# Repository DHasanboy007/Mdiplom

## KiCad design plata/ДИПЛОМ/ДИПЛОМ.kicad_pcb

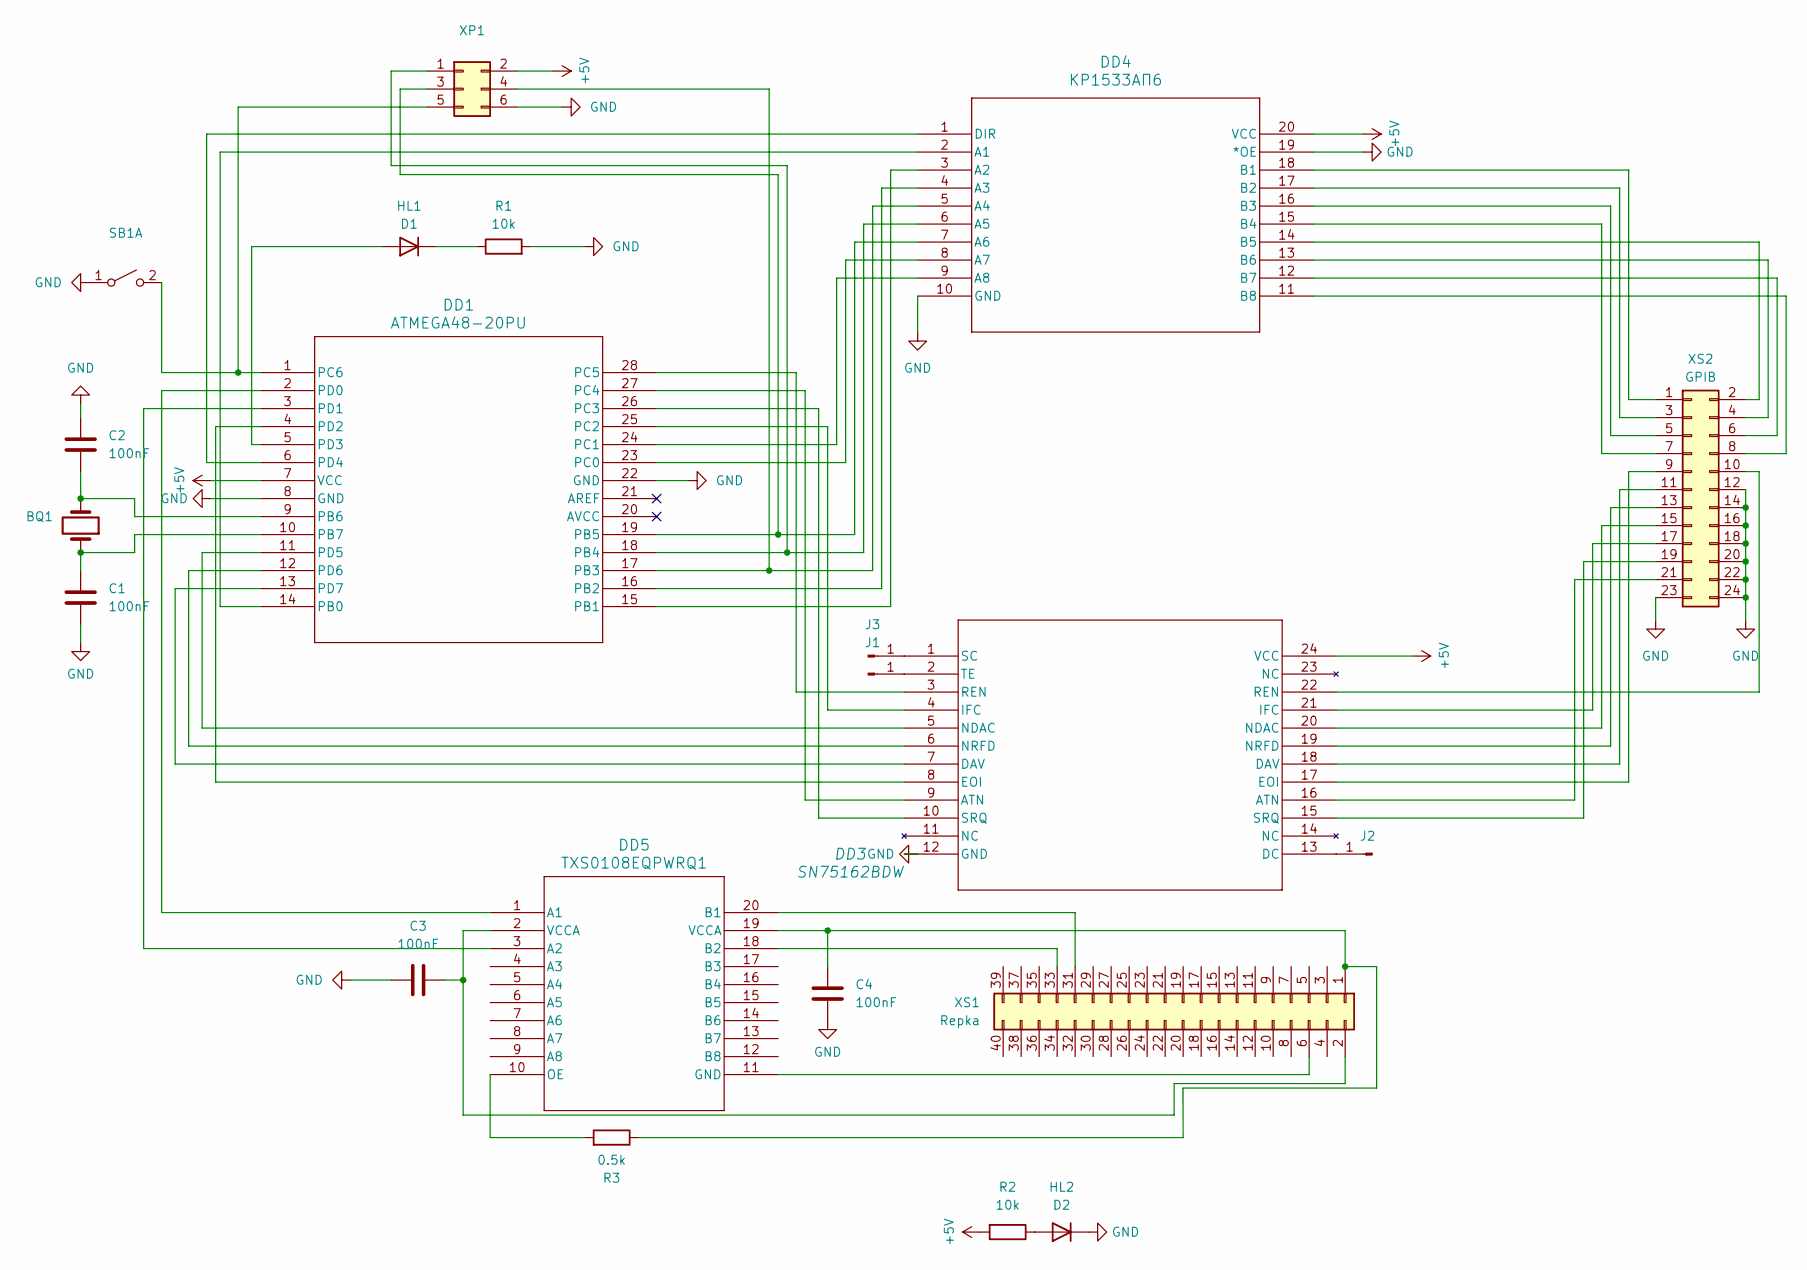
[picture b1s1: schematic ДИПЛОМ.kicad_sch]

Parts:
BQ1: Crystal; Crystal_HC49-U_Vertical
C1, C2, C3, C4: 100nF; C_0805_2012Metric
DD1: ATMEGA48-20PU; DIP-28_W7.62mm_SMDSocket_SmallPads
DD3: SN75162BDW; SOIC-24W_7.5x15.4mm_P1.27mm
DD4: КР1533АП6; DIP-20_W7.62mm
DD5: TXS0108EQPWRQ1; TSSOP-20_4.4x6.5mm_P0.65mm
HL1: D1; D_SOD-123
HL2: D2; D_SOD-123
J1, J2, J3: Conn_01x01_Pin; PinHeader_1x01_P2.54mm_Vertical
R1, R2: 10k; R_0805_2012Metric
R3: 0.5k; R_0805_2012Metric
SB1: SW_DPST_x2; SW_Push_1P1T_NO_E-Switch_TL3301NxxxxxG
XP1: Conn_02x03_Odd_Even; PinHeader_2x03_P2.54mm_Vertical
XS1: Repka; PinSocket_2x20_P2.54mm_Vertical
XS2: GPIB; PinSocket_2x12_P2.54mm_Vertical

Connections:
+5V: DD1.7 (VCC), DD3.24 (VCC), DD4.20 (VCC), R2.2, XP1.2
GND: C1.2, C2.1, C3.2, C4.2, DD1.8 (GND), DD1.22 (GND), DD3.12 (GND), DD4.10 (GND), DD4.19 (*OE), HL2.1 (K), R1.2, SB1.1 (A), XP1.6, XS2.12, XS2.14, XS2.16, XS2.18, XS2.20, XS2.22, XS2.23, XS2.24
unnamed: DD1.14 (PB0), DD4.2 (A1)
unnamed: DD1.15 (PB1), DD4.3 (A2)
unnamed: DD1.16 (PB2), DD4.4 (A3)
unnamed: DD1.17 (PB3), DD4.5 (A4), XP1.4
unnamed: DD1.18 (PB4), DD4.6 (A5), XP1.1
unnamed: DD1.19 (PB5), DD4.7 (A6), XP1.3
unnamed: BQ1.2, C2.2, DD1.9 (PB6)
unnamed: BQ1.1, C1.1, DD1.10 (PB7)
unnamed: DD1.23 (PC0), DD4.8 (A7)
unnamed: DD1.24 (PC1), DD4.9 (A8)
unnamed: DD1.25 (PC2), DD3.4 (IFC)
unnamed: DD1.26 (PC3), DD3.10 (SRQ)
unnamed: DD1.27 (PC4), DD3.9 (ATN)
unnamed: DD1.28 (PC5), DD3.3 (REN)
unnamed: DD1.1 (PC6), SB1.2 (B), XP1.5
unnamed: DD1.2 (PD0), DD5.1 (A1)
unnamed: DD1.3 (PD1), DD5.3 (A2)
unnamed: DD1.4 (PD2), DD3.8 (EOI)
unnamed: DD1.5 (PD3), HL1.2 (A)
unnamed: DD1.6 (PD4), DD4.1 (DIR)
unnamed: DD1.11 (PD5), DD3.5 (NDAC)
unnamed: DD1.12 (PD6), DD3.6 (NRFD)
unnamed: DD1.13 (PD7), DD3.7 (DAV)
unnamed: DD3.13 (DC), J2.1
unnamed: DD3.1 (SC), J3.1
unnamed: DD3.2 (TE), J1.1
unnamed: DD4.18 (B1), XS2.1
unnamed: DD4.17 (B2), XS2.3
unnamed: DD4.16 (B3), XS2.5
unnamed: DD4.15 (B4), XS2.7
unnamed: DD4.14 (B5), XS2.2
unnamed: DD4.13 (B6), XS2.4
unnamed: DD4.12 (B7), XS2.6
unnamed: DD4.11 (B8), XS2.8
unnamed: DD5.20 (B1), XS1.31
unnamed: DD5.18 (B2), XS1.33
unnamed: DD5.11 (GND), XS1.6
unnamed: DD5.10 (OE), R3.2
unnamed: HL1.1 (K), R1.1
unnamed: HL2.2 (A), R2.1
unnamed: C4.1, DD5.19 (VCCA), R3.1, XS1.1
unnamed: C3.1, DD5.2 (VCCA), XS1.2
unnamed: DD3.17 (EOI), XS2.9
unnamed: DD3.22 (REN), XS2.10
unnamed: DD3.18 (DAV), XS2.11
unnamed: DD3.19 (NRFD), XS2.13
unnamed: DD3.20 (NDAC), XS2.15
unnamed: DD3.21 (IFC), XS2.17
unnamed: DD3.15 (SRQ), XS2.19
unnamed: DD3.16 (ATN), XS2.21

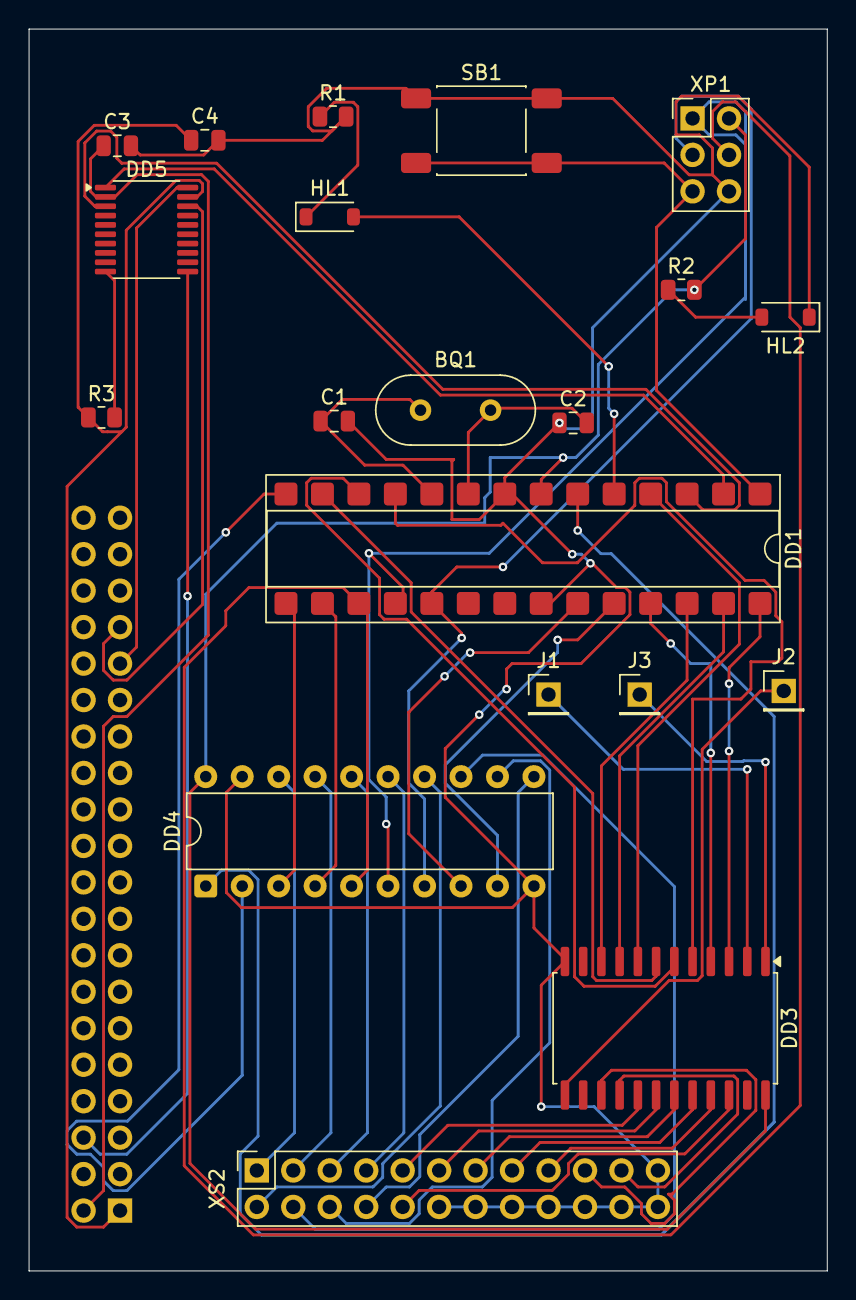
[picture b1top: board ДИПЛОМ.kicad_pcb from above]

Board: 2 copper layers, 55.6 x 86.5 mm, 21 parts (1 on the bottom side), 52 nets.

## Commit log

2026-06-03 vault backup: 2026-06-04 02:35:15
2026-06-05 Diplom layihasi fayllari qo'shildi
2026-06-05 vault backup: 2026-06-05 11:09:27
